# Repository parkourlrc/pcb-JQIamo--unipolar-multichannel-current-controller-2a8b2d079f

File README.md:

# unipolar-multichannel-current-controller
A high-stability unipolar current controller with full digital control and arbitrary number of channels.

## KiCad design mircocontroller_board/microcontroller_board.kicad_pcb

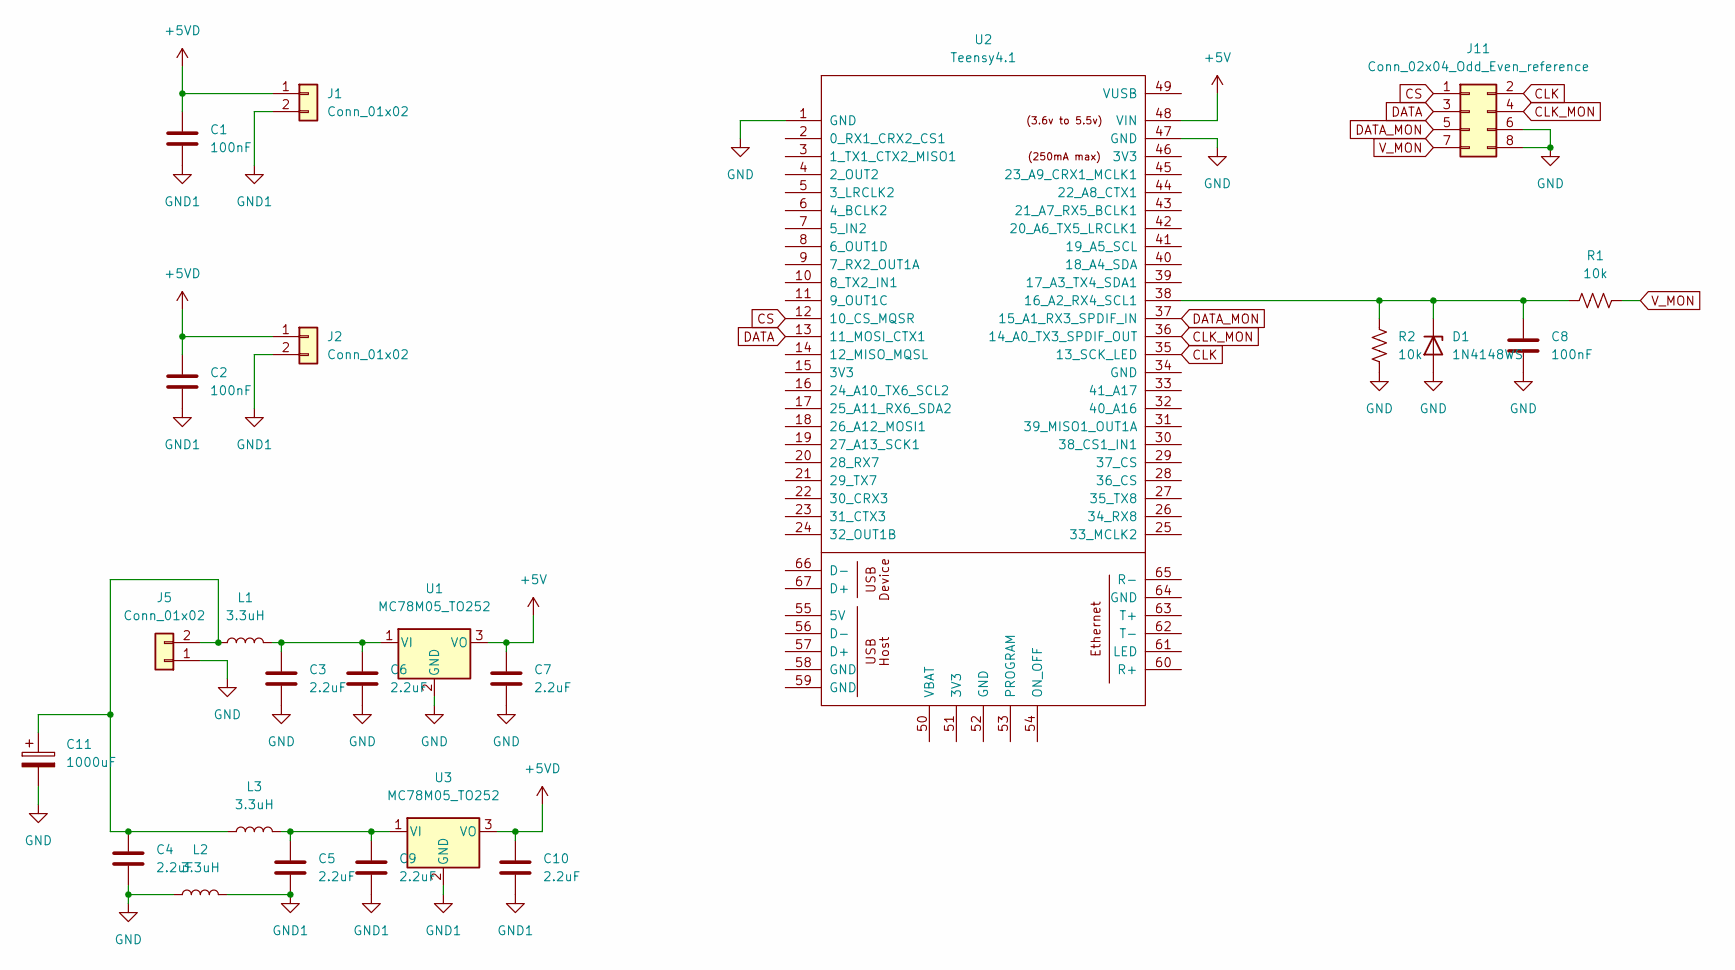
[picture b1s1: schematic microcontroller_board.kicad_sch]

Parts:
C1, C2, C8: 100nF; C_0603_1608Metric
C3, C4, C5, C6, C7, C9, C10: 2.2uF; C_0603_1608Metric
C11: 1000uF; CP_Radial_D10.0mm_P5.00mm
D1: 1N4148WS; D_SOD-323
J1, J2, J5: Conn_01x02; PhoenixContact_MCV_1,5_2-G-3.5_1x02_P3.50mm_Vertical
J11: Conn_02x04_Odd_Even_reference; IDC-Header_2x04_P2.54mm_Vertical
L1, L2, L3: 3.3uH; IHLP3232
R1, R2: 10k; R_0603_1608Metric
U1, U3: MC78M05_TO252; TO-252-2
U2: Teensy4.1; Teensy41

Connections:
+5V: C7.1, U1.3 (VO), U2.48 (VIN)
+5VD: C1.1, C2.1, C10.1, J1.1, J2.1, U3.3 (VO)
CLK: J11.2, U2.35 (13_SCK_LED)
CLK_MON: J11.4, U2.36 (14_A0_TX3_SPDIF_OUT)
CS: J11.1, U2.12 (10_CS_MQSR)
DATA: J11.3, U2.13 (11_MOSI_CTX1)
DATA_MON: J11.5, U2.37 (15_A1_RX3_SPDIF_IN)
GND: C3.2, C4.2, C6.2, C7.2, C8.2, C11.2, D1.2 (A), J5.1, J11.6, J11.8, L2.1, R2.2, U1.2 (GND), U2.1 (GND), U2.47 (GND)
GND1: C1.2, C2.2, C5.2, C9.2, C10.2, J1.2, J2.2, L2.2, U3.2 (GND)
unnamed: C3.1, C6.1, L1.2, U1.1 (VI)
unnamed: C5.1, C9.1, L3.2, U3.1 (VI)
unnamed: C8.1, D1.1 (K), R1.2, R2.1, U2.38 (16_A2_RX4_SCL1)
unnamed: C4.1, C11.1, J5.2, L1.1, L3.1
V_MON: J11.7, R1.1

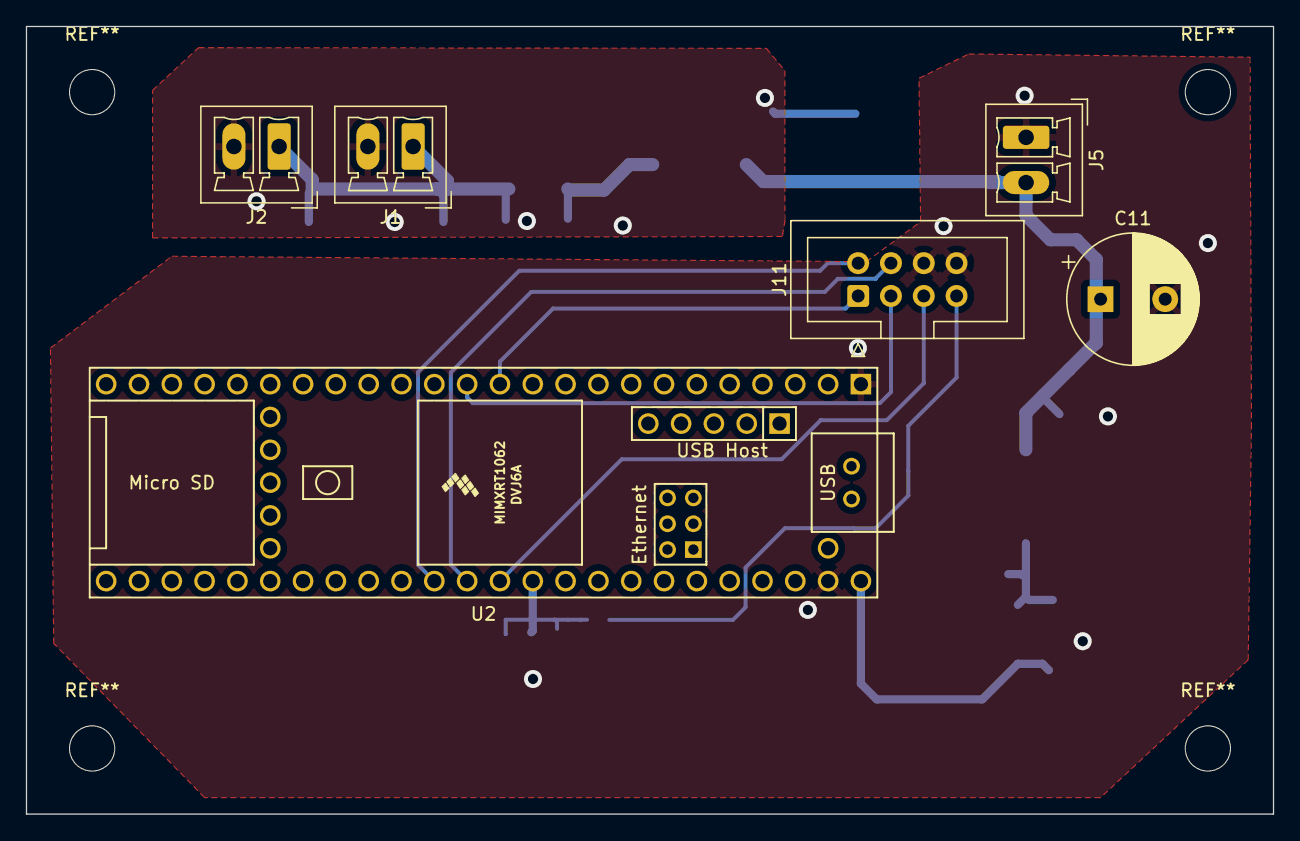
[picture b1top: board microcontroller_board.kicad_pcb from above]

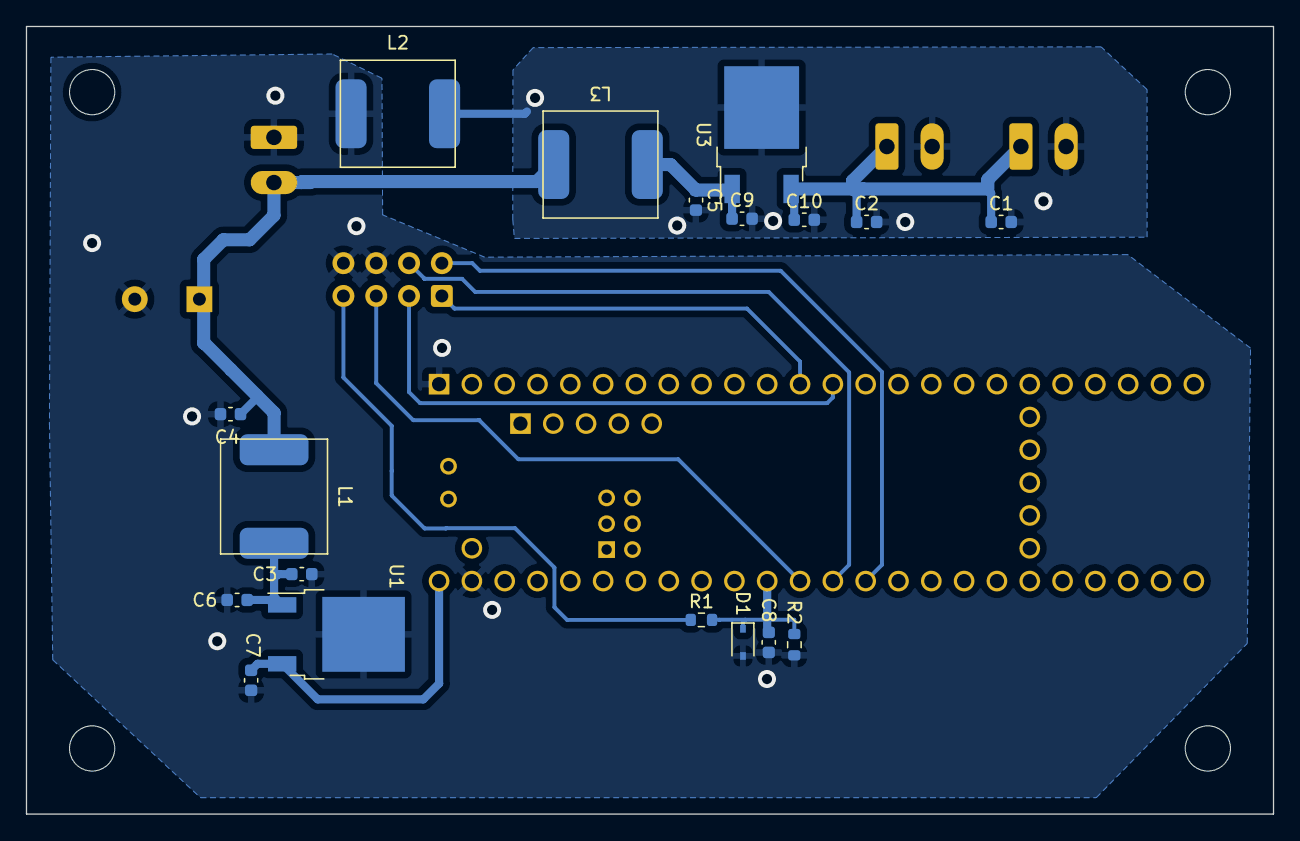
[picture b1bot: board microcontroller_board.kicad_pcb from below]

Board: 2 copper layers, 96.5 x 61.0 mm, 24 parts (18 on the bottom side), 14 nets.

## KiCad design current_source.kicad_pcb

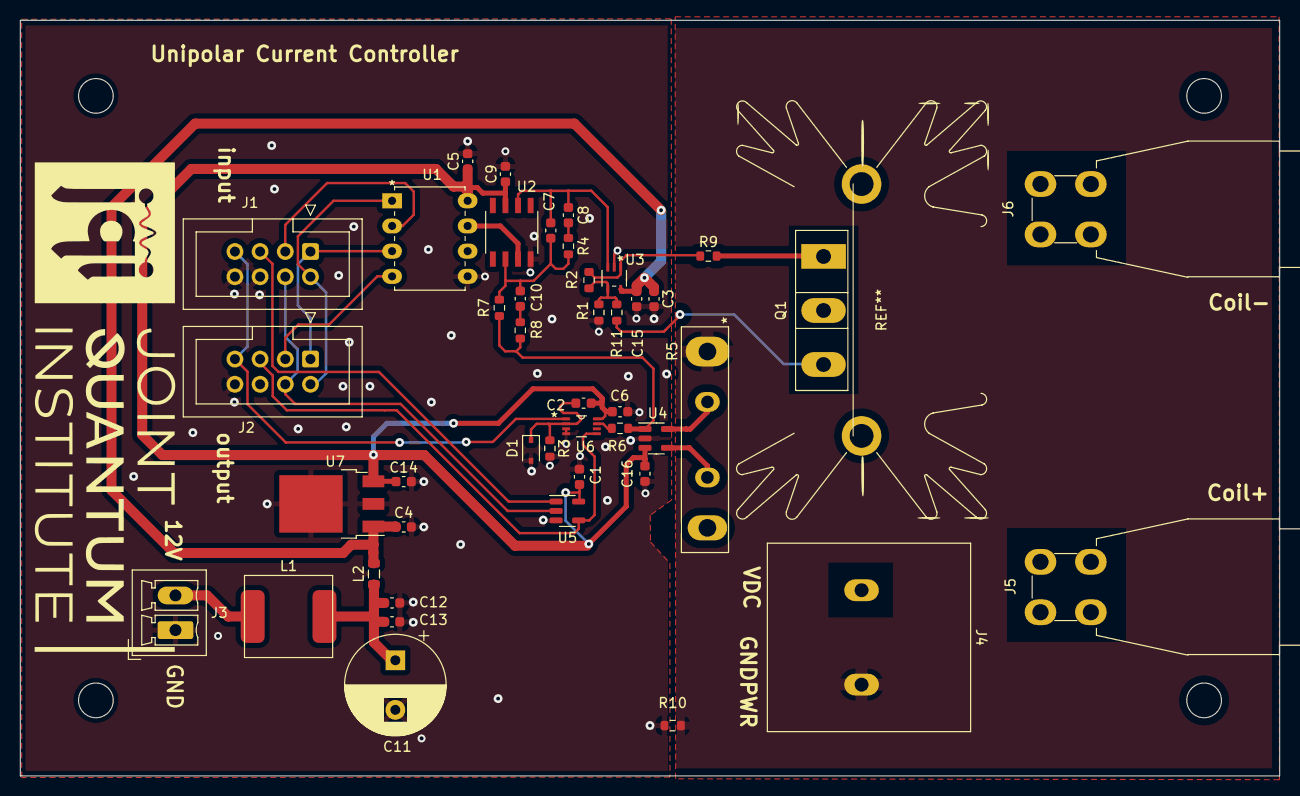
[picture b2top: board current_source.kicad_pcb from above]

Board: 2 copper layers, 127.0 x 76.2 mm, 44 parts (0 on the bottom side), 30 nets.

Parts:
C1, C2, C5, C6, C9, C15, C16: 100nF; C_0603_1608Metric
C3, C4, C13, C14: 2.2uF; C_0603_1608Metric
C7: 10nF; C_0603_1608Metric
C8, C10: DNP; C_0603_1608Metric
C11: 1000uF; CP_Radial_D10.0mm_P5.00mm
C12: 15uF; C_0603_1608Metric
D1: 1N4148WS; D_SOD-323
J1, J2: Conn_02x04_Odd_Even; IDC-Header_2x04_P2.54mm_Vertical
J3: Conn_01x02_small; PhoenixContact_MCV_1,5_2-G-3.5_1x02_P3.50mm_Vertical
J4: Conn_01x02_big; ESPM02230_9.35mm
J5: Conn_01x01_white; CalTest_CT3151
J6: Conn_01x01_black; CalTest_CT3151
L1: 3.3uH; IHLP3232
L2: 1k; L_0805_2012Metric
Q1: NTHL095N65S3H; TO-247-3_Vertical
R1, R3, R6, R7: 10k; R_0603_1608Metric
R2: 20k; R_0603_1608Metric
R4, R8, R11: DNP; R_0603_1608Metric
R5: 10m; FHR4V-0R002F1
R9: 6; R_0603_1608Metric
R10: 100; R_0603_1608Metric
U1: LTC1655CN8-PBF
U2: OPA388ID
U3: OPA810IDCKR; TSV621ICT-SC70-5
U4: INA293BX; SOT-23-5
U5: SN74LVC1G79DBVR; SOT-23-5
U6: SN74LVC2G53DCUR
U7: MC78M05CDTRKG; TO-252-3_TabPin2

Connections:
+5V: C1.1, C2.1, C5.1, C6.1, C9.1, C14.1, C16.1, U1.8 (VCC), U2.7 (V+), U4.3 (V+), U5.5 (VCC), U6.8 (VCC), U7.3 (VO)
+12V: C3.1, C4.1, C15.1, L2.2, U3.5 (V+), U7.1 (VI)
+VDC: J4.1, J5.1
CLK_MON: J1.4, J2.4, U5.2 (C)
CLK_SPI: J1.2, J2.2, U1.1 (CLK)
CS: J1.1, J2.1, U1.3 (*CS/LD)
DIN_MON: J1.5, U5.1 (D)
DIN_SPI: J1.3, U1.2 (DIN)
DOUT_MON: J2.5, U5.4 (Q), U6.5 (A)
DOUT_SPI: J2.3, U1.4 (DOUT)
GND: C1.2, C3.2, C4.2, C5.2, C6.2, C9.2, C11.2, C12.2, C13.2, C14.2, C15.2, C16.2, D1.2 (A), J1.6, J1.8, J2.6, J2.8, J3.1, R1.2, R3.2, R10.1, U1.5 (GND), U2.4 (V-), U3.2 (V-), U4.2 (V-), U5.3 (GND), U6.3 (GND), U6.4 (GND), U7.2 (GND)
GNDPWR: J4.2, R5.1, R10.2
unnamed: C7.2, C8.2, U2.6, U3.3 (+)
unnamed: C8.1, R4.2
unnamed: C7.1, C10.1, R4.1, R7.1, U2.2 (-)
unnamed: C10.2, R8.1
unnamed: C11.1, C12.1, C13.1, L1.2, L2.1
unnamed: J3.2, L1.1
unnamed: J6.1, Q1.2 (D)
unnamed: Q1.1 (G), R9.2
unnamed: Q1.3 (S), R5.15, R11.2
unnamed: R1.1, R2.1, R11.1, U3.4 (-)
unnamed: R2.2, R9.1, U3.1
unnamed: R5.5, U4.5 (-)
unnamed: R5.11, U4.4 (+)
unnamed: R6.1, U6.7 (Y1)
unnamed: R6.2, R7.2, R8.2, U4.1
unnamed: U1.7 (VOUT), U2.3 (+)
V_MON: J1.7, J2.7, U6.1 (COM)
reset: C2.2, D1.1 (K), R3.1, U6.2 (INH)

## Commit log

2025-06-30 KiCad files for current control circuit
2025-06-30 Rename current_source_footprints.pretty to current_source/current_source_footprints.pretty
2025-06-30 Rename download_library to current_source/download_library
2025-06-30 Update and rename fp-lib-table to current_source/fp-lib-table
2025-06-30 Rename schematic.pdf to current_source/schematic.pdf
2025-06-30 current source circuit - pretty files and library files
2025-06-30 microcontroller board circuit
2025-06-30 control arduino codes (Teensy 4.1)
2025-06-30 python program for controlling current
2025-07-14 Added LICENSE.txt with CERN-OHL-S strongly reciprocal license

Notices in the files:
parts and their libraries:
Copyright 2021 Accelerated Designs. All rights reserved.
